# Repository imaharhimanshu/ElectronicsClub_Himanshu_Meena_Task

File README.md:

# ElectronicsClub_Himanshu_Meena_Task

Microcontroller Inputs, Outputs

System Overview and Inputs  
The main part of this electronic dice project is an Arduino Nano, which acts as the brain of the system and runs on a standard 5V supply. For physical input, the setup uses a  push button. This button is connected directly between one of the Arduino digital input pins and the circuit ground.  

System Outputs  
For the output the arduino uses seven digital pins to control seven individual leds. These leds are arranged on the physical board to visually like dice face. To prevent the components from burning out, each LED has a current-limiting resistor that keeps the operating current at a safe 15mA.  

How the Logic Works  
The operation of the dice is simple. When a user presses the button, it connects the input pin to ground, which the Arduino recognizes as a signal. After detecting the button press the microcontroller runs a routine to select a random number between 1 and 6. Based on the number it generates, the Arduino determines which combination of the seven output pins to activate. It turns on those selected pins, lighting up the corresponding LEDs to show the final result of the dice roll to the user.o display the final dice roll to the user.

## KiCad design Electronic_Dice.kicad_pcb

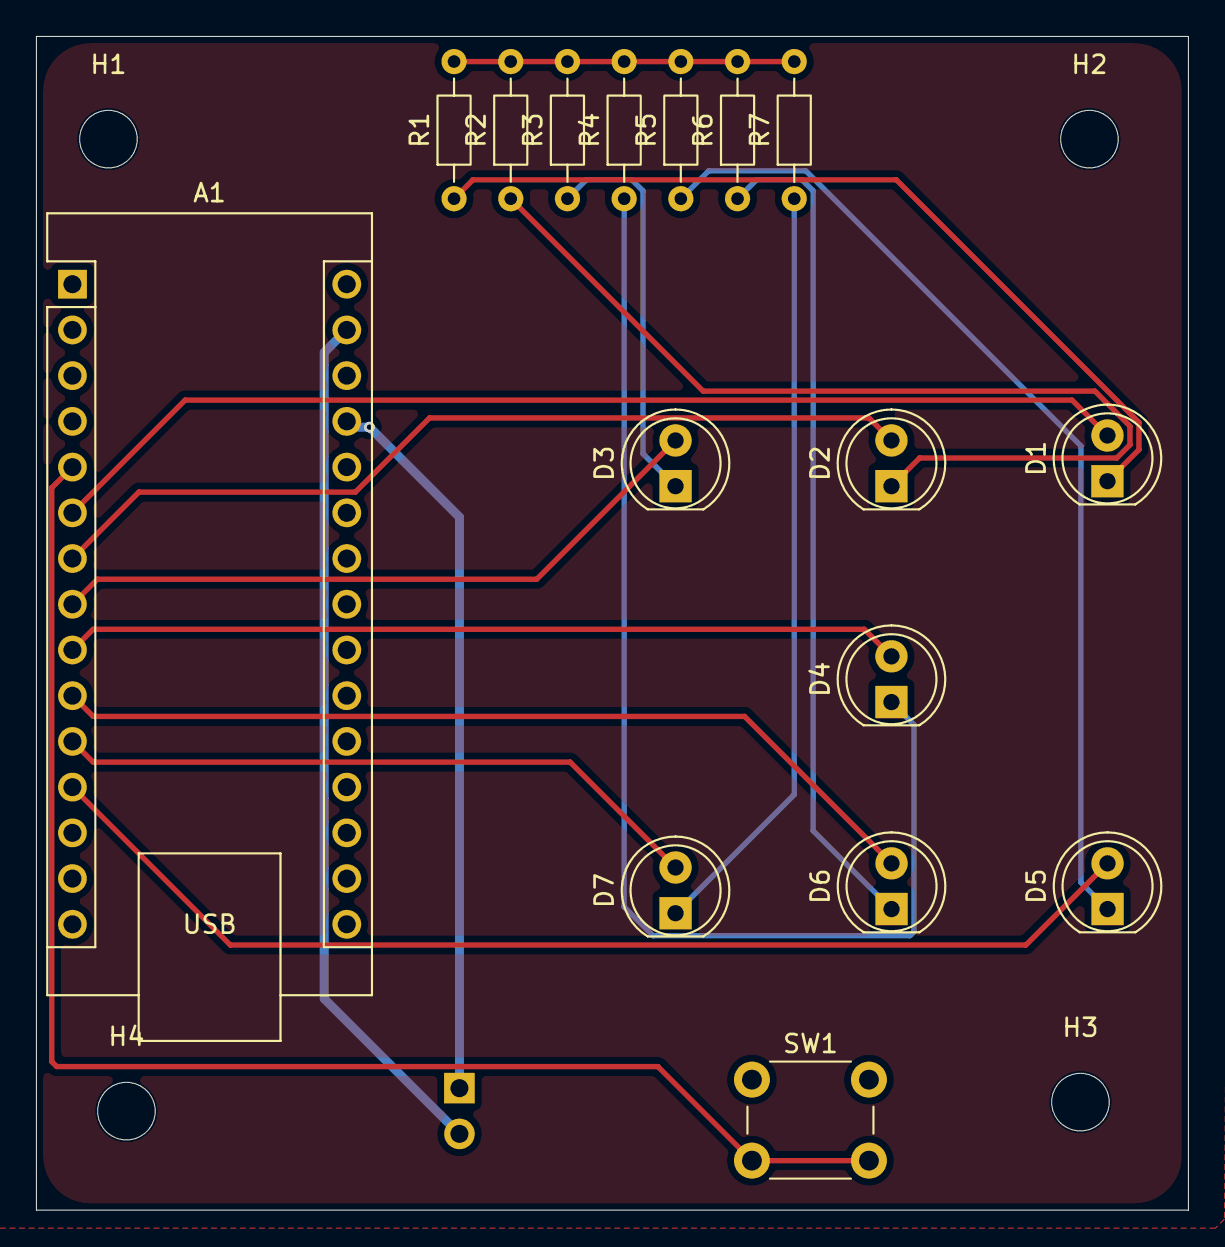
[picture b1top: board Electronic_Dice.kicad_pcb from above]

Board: 2 copper layers, 64.0 x 65.2 mm, 21 parts (1 on the bottom side), 18 nets.

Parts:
A1: Arduino_Nano_v3.x; Arduino_Nano
D1, D2, D3, D4, D5, D6, D7: LED; LED_D5.0mm
H1, H2, H3, H4: MountingHole; MountingHole_3.2mm_M3
J1: Conn_01x02; PinHeader_1x02_P2.54mm_Vertical
R1, R2, R3, R4, R5, R6, R7: 200R; R_Axial_DIN0204_L3.6mm_D1.6mm_P7.62mm_Horizontal
SW1: SW_MEC_5E; SW_PUSH_6mm

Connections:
/D3: A1.6 (D3), D1.2 (A)
/D4: A1.7 (D4), D2.2 (A)
/D5: A1.8 (D5), D3.2 (A)
/D6: A1.9 (D6), D4.2 (A)
/D7: A1.10 (D7), D6.2 (A)
/D8: A1.11 (D8), D7.2 (A)
/D9: A1.12 (D9), D5.2 (A)
GND: R1.2, R2.2, R3.2, R4.2, R5.2, R6.2, R7.2
unnamed: A1.27 (+5V), J1.1
unnamed: A1.5 (D2), SW1.2 (2_2)
unnamed: D1.1 (K), R1.1
unnamed: D2.1 (K), R2.1
unnamed: D3.1 (K), R3.1
unnamed: D4.1 (K), R4.1
unnamed: D5.1 (K), R5.1
unnamed: D6.1 (K), R6.1
unnamed: D7.1 (K), R7.1
unnamed: A1.29 (GND), J1.2
